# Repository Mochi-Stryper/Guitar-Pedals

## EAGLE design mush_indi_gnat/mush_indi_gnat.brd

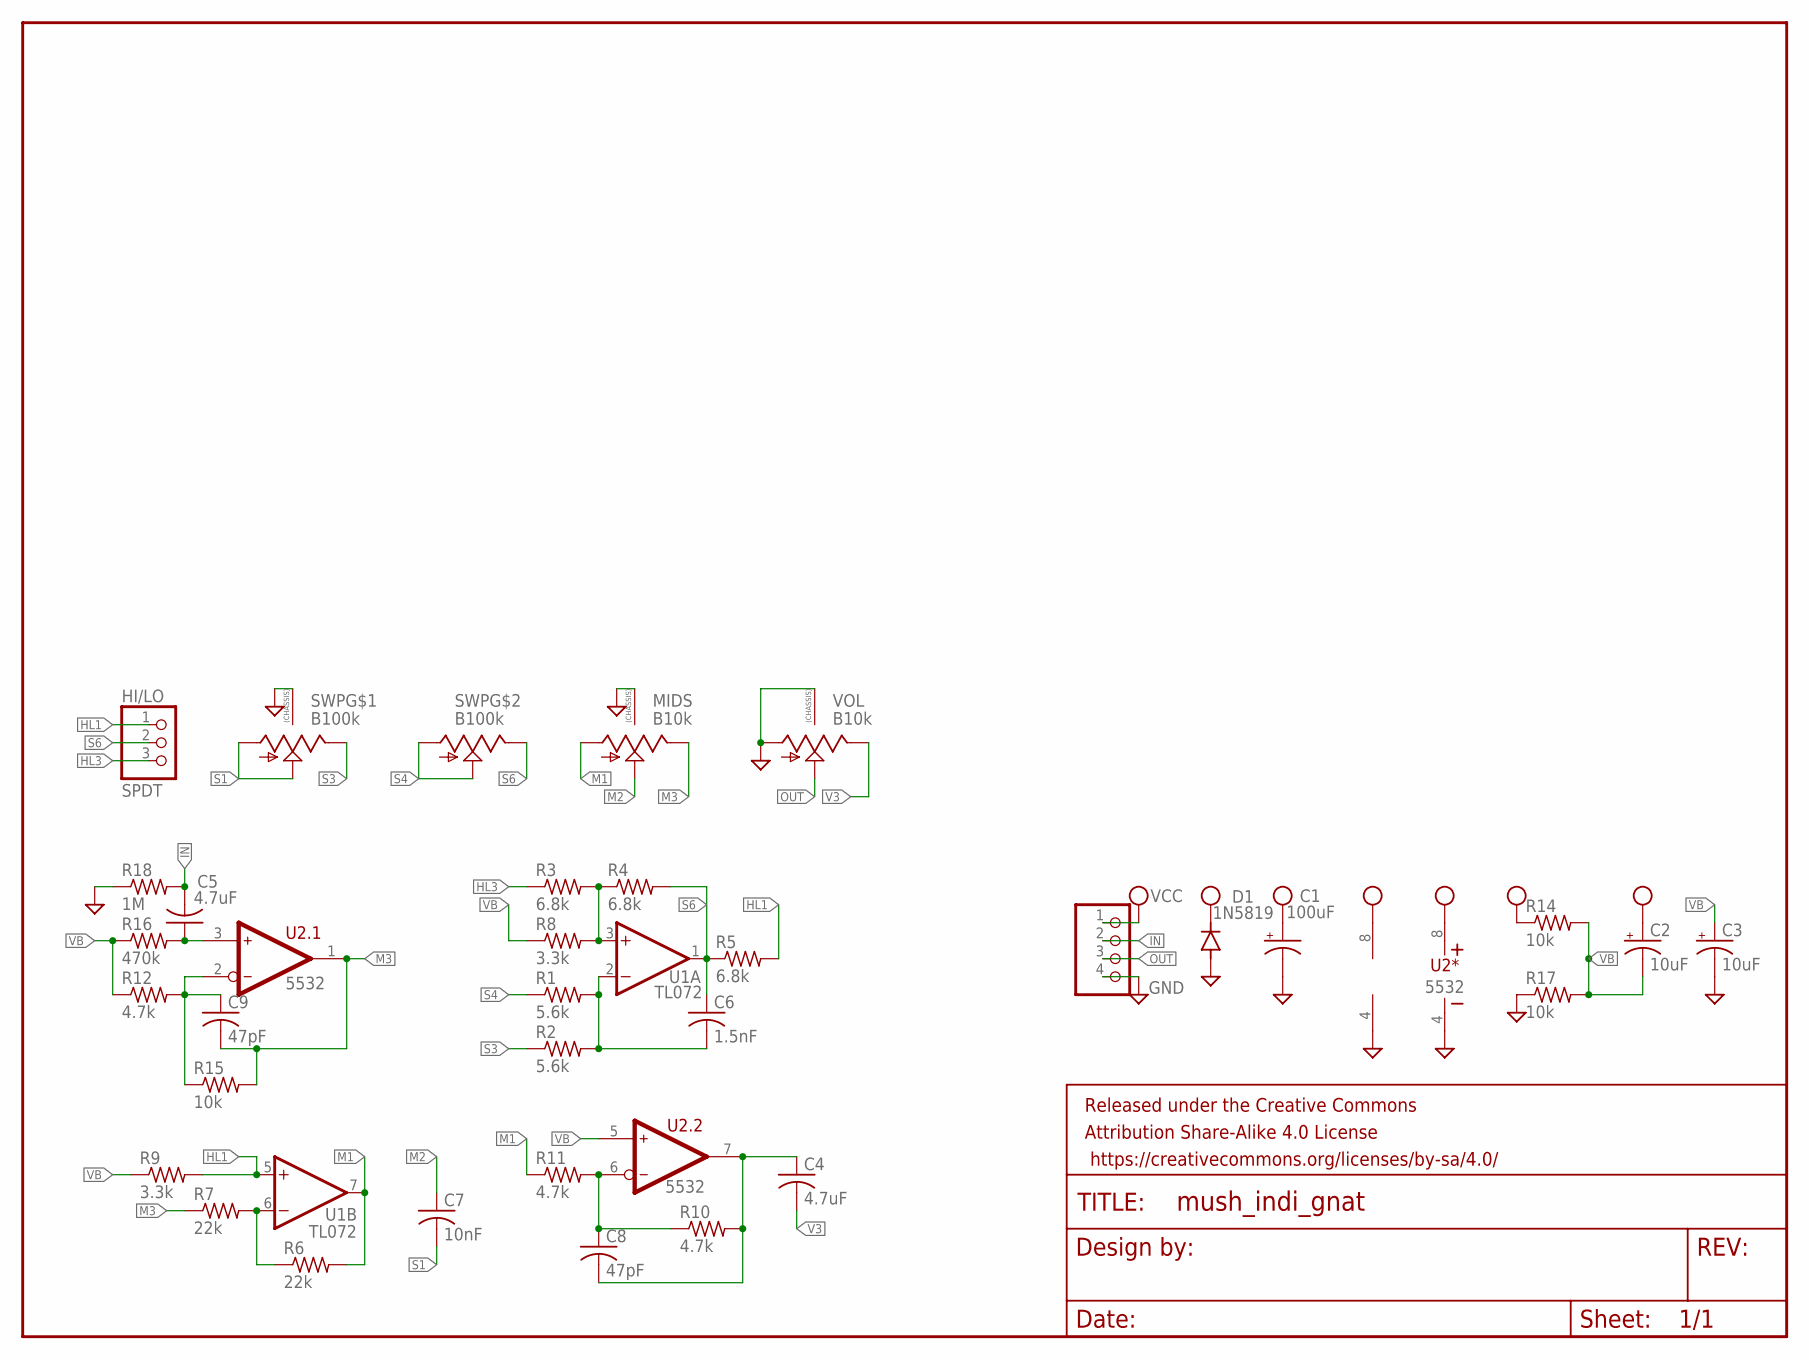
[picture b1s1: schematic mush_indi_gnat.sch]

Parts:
C1: 100uF; PAN_B_SMD+THRU
C2, C3: 10uF; CAPMP3216X180N
C4, C5: 4.7uF; C0805
C6: 1.5nF; C0603
C7: 10nF; C0603
C8, C9: 47pF; C0603
D1: 1N5819; SOD123
FRAME1: FRAME-LETTERNO_PACKAGE; DUMMY
HI/LO: SPDT; 1X03
JP1: PINHD-1X4; 1X04
MIDS: B10k; 9MM_SNAP-IN_POT
R1, R2: 5.6k; R0603
R3, R4, R5: 6.8k; R0603
R6, R7: 22k; R0603
R8, R9: 3.3k; R0603
R10, R11, R12: 4.7k; R0603
R14, R15, R17: 10k; R0603
R16: 470k; R0603
R18: 1M; R0603
SWP: B100k; DUAL_9MM_SNAP-IN_POT
U1: TL072; TSSOP-8
U2: 5532; SO-8
VOL: B10k; 9MM_SNAP-IN_POT

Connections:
GND: C1.-, C1.-- (-), C3.2 (-), D1.A, JP1.4, MIDS.CHASSIS1, MIDS.CHASSIS2, R17.1, R18.1, SWP.CHASSIS1, SWP.CHASSIS2, U1.4 (V-), U2.4 (V-), VOL.1 (A), VOL.CHASSIS1, VOL.CHASSIS2
HL1: HI/LO.1, R5.2, R9.2, U1.5 (+IN)
HL3: HI/LO.3, R3.1
IN: C5.2, JP1.2, R18.2
M1: MIDS.1 (A), R6.2, R11.1, U1.7 (OUT)
M2: C7.1, MIDS.2 (S)
M3: C9.2, MIDS.3 (E), R7.1, R15.2, U2.1 (OUT)
unnamed: C5.1, R16.2, U2.3 (IN+)
unnamed: C9.1, R12.2, R15.1, U2.2 (IN-)
unnamed: R6.1, R7.2, U1.6 (-IN)
unnamed: R3.2, R4.1, R8.2, U1.3 (+IN)
unnamed: C6.2, R1.2, R2.2, U1.2 (-IN)
unnamed: C8.1, R10.1, R11.2, U2.6 (IN-)
unnamed: C4.1, C8.2, R10.2, U2.7 (OUT)
OUT: JP1.3, VOL.2 (S)
S1: C7.2, SWP.1 (A), SWP.2 (S)
S3: R2.1, SWP.3 (E)
S4: R1.1, SWP.1B (A), SWP.2B (S)
S6: C6.1, HI/LO.2, R4.2, R5.1, SWP.3B (E), U1.1 (OUT)
V3: C4.2, VOL.3 (E)
VB: C2.2 (-), C3.1 (+), R8.1, R9.1, R12.1, R14.2, R16.1, R17.2, U2.5 (IN+)
VCC: C1.+, C1.++ (+), C2.1 (+), D1.C, JP1.1, R14.1, U1.8 (V+), U2.8 (V+)

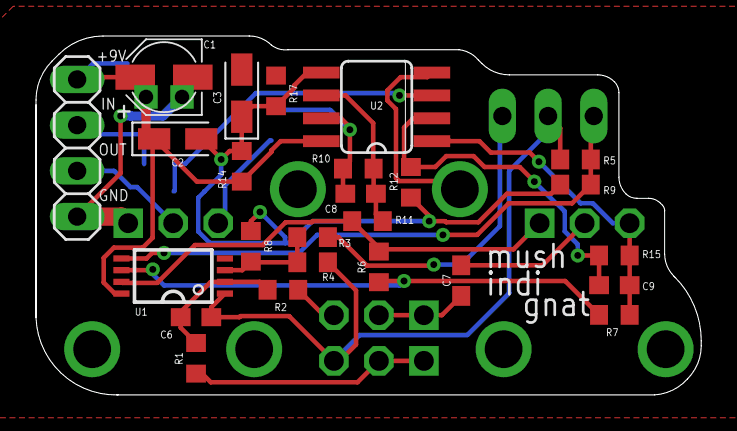
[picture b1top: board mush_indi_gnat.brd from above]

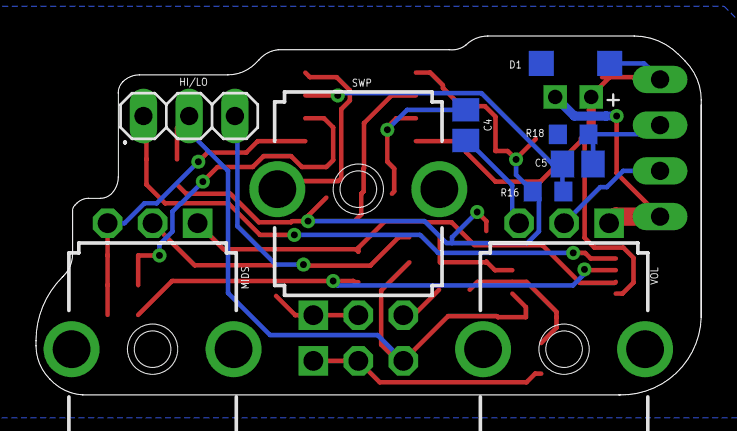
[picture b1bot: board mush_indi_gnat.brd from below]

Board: 2 copper layers, 37.0 x 19.9 mm, 35 parts (9 on the bottom side), 22 nets.

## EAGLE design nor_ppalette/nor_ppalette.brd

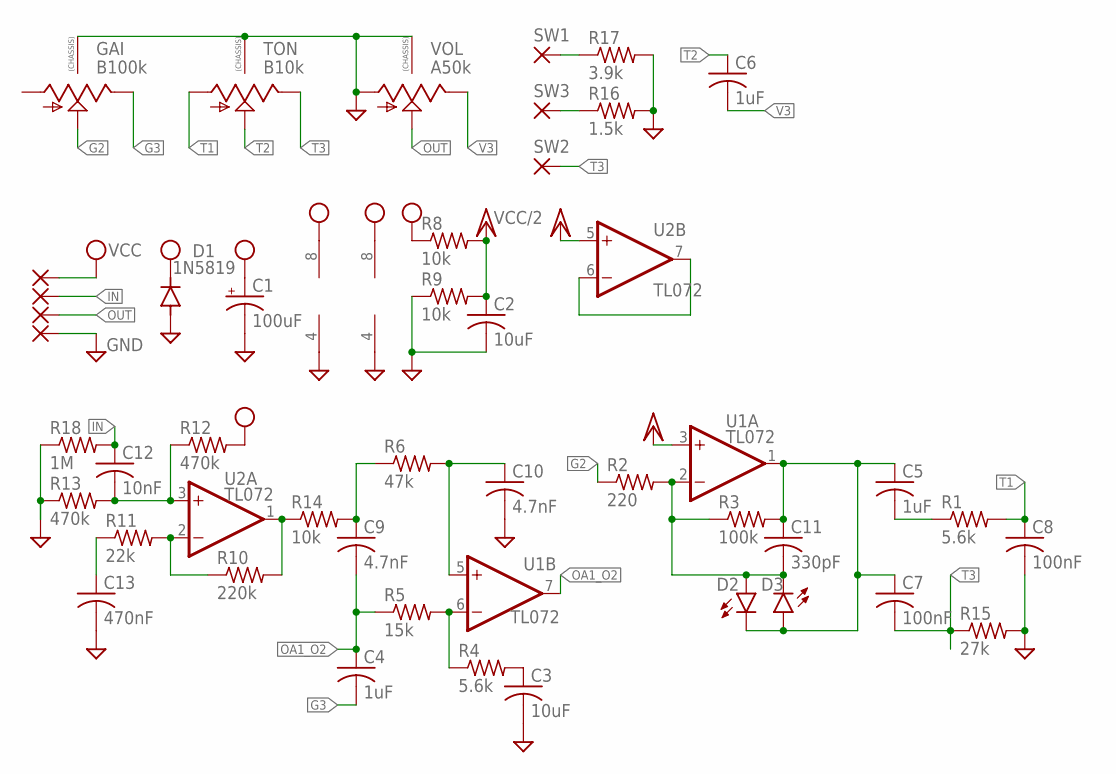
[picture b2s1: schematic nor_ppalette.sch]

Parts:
C1: 100uF; CPOL-RADIAL-2.5MM-6.5MM
C2, C3: 10uF; C1206
C4, C5, C6: 1uF; C0805
C7, C8: 100nF; C0603
C9, C10: 4.7nF; C0603
C11: 330pF; C0603
C12: 10nF; C0603
C13: 470nF; C0603
D1: 1N5819; SOD123
D2, D3: LED0603; LED-0603
GAI: B100k; 9MM_SNAP-IN_POT
PAD1, PAD2, PAD3, PAD4: 1,6/0,8
R1, R4: 5.6k; R0603
R2: 220; R0603
R3: 100k; R0603
R5: 15k; R0603
R6: 47k; R0603
R8, R9, R14: 10k; R0603
R10: 220k; R0603
R11: 22k; R0603
R12, R13: 470k; R0603
R15: 27k; R0603
R16: 1.5k; R0603
R17: 3.9k; R0603
R18: 1M; R0603
SW1, SW2, SW3: 1,6/0,8
TON: B10k; 9MM_SNAP-IN_POT
U1, U2: TL072; TSSOP-8
VOL: A50k; 9MM_SNAP-IN_POT

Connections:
G2: GAI.2 (S), R2.1
G3: C4.2, GAI.3 (E)
GND: C1.2 (-), C2.2, C3.2, C8.2, C10.2, C13.2, D1.A, GAI.CHASSIS1, GAI.CHASSIS2, PAD4.1, R9.1, R13.1, R15.2, R16.2, R17.2, R18.1, TON.CHASSIS1, TON.CHASSIS2, U1.4 (V-), U2.4 (V-), VOL.1 (A), VOL.CHASSIS1, VOL.CHASSIS2
IN: C12.1, PAD2.1, R18.2
unnamed: R10.1, R11.2, U2.2 (-IN)
unnamed: U2.6 (-IN), U2.7 (OUT)
unnamed: C12.2, R12.1, R13.2, U2.3 (+IN)
unnamed: R10.2, R14.1, U2.1 (OUT)
unnamed: C13.1, R11.1
unnamed: C9.1, R6.1, R14.2
unnamed: C10.1, R6.2, U1.5 (+IN)
unnamed: R4.1, R5.2, U1.6 (-IN)
unnamed: C3.1, R4.2
unnamed: C5.1, C7.1, C11.1, D2.C, D3.A, R3.2, U1.1 (OUT)
unnamed: C11.2, D2.A, D3.C, R2.2, R3.1, U1.2 (-IN)
unnamed: C5.2, R1.1
unnamed: R17.1, SW1.1
unnamed: R16.1, SW3.1
OA1_O2: C4.1, C9.2, R5.1, U1.7 (OUT)
OUT: PAD3.1, VOL.2 (S)
T1: C8.1, R1.2, TON.1 (A)
T2: C6.1, TON.2 (S)
T3: C7.2, R15.1, SW2.1, TON.3 (E)
V3: C6.2, VOL.3 (E)
VCC: C1.1 (+), D1.C, PAD1.1, R8.1, R12.2, U1.8 (V+), U2.8 (V+)
VCC/2: C2.1, R8.2, R9.2, U1.3 (+IN), U2.5 (+IN)

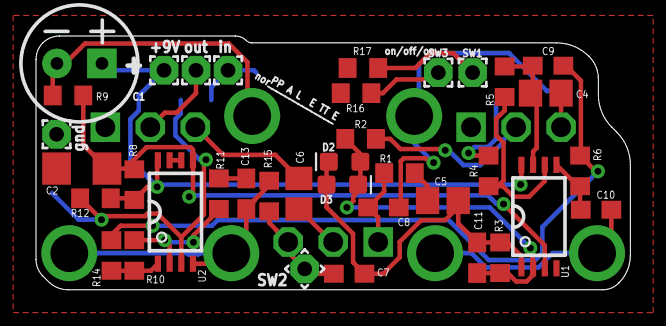
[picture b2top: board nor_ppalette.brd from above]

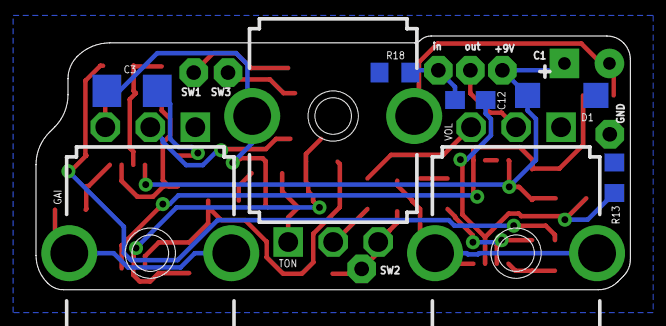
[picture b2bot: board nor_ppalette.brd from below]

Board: 2 copper layers, 33.0 x 14.1 mm, 45 parts (8 on the bottom side), 26 nets.

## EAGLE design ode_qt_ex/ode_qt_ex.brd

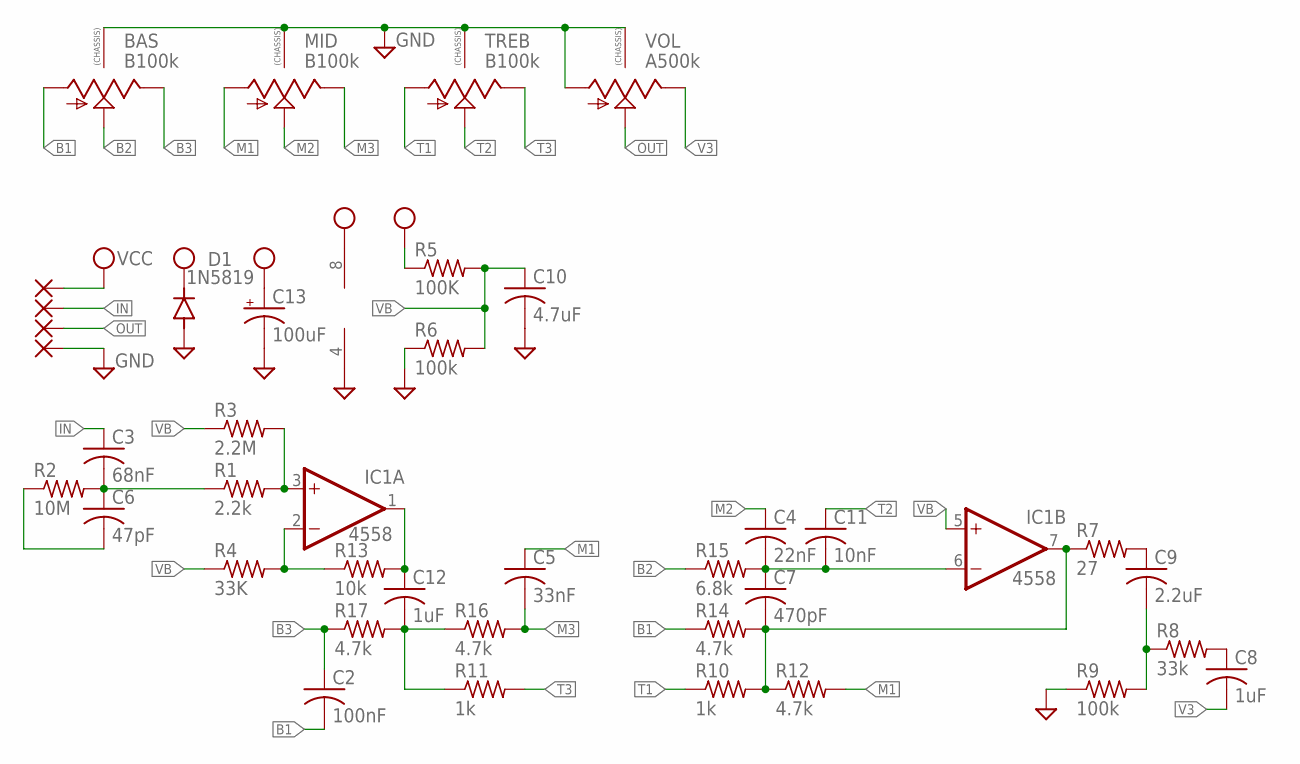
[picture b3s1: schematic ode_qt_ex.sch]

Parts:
BAS: B100k; 9MM_SNAP-IN_POT
C2: 100nF; C0603
C3: 68nF; C0603
C4: 22nF; C0603
C5: 33nF; C0603
C6: 47pF; C0603
C7: 470pF; C0603
C8, C12: 1uF; C0603
C9: 2.2uF; C0805
C10: 4.7uF; C0805
C11: 10nF; C0603
C13: 100uF; CPOL-RADIAL-2.5MM-6.5MM
D1: 1N5819; SOD123
IC1: 4558; SO08
MID: B100k; 9MM_SNAP-IN_POT
PAD1, PAD2, PAD3, PAD4: 1,6/0,8
R1: 2.2k; R0603
R2: 10M; R0603
R3: 2.2M; R0603
R4: 33K; R0603
R5: 100K; R0603
R6, R9: 100k; R0603
R7: 27; R0603
R8: 33k; R0603
R10, R11: 1k; R0603
R12, R14, R16, R17: 4.7k; R0603
R13: 10k; R0603
R15: 6.8k; R0603
TREB: B100k; 9MM_SNAP-IN_POT
VOL: A500k; 9MM_SNAP-IN_POT

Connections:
B1: BAS.1 (A), C2.2, R14.1
B2: BAS.2 (S), R15.1
B3: BAS.3 (E), C2.1, R17.1
GND: BAS.CHASSIS1, BAS.CHASSIS2, C10.2, C13.2 (-), D1.A, IC1.4 (V-), MID.CHASSIS1, MID.CHASSIS2, PAD4.1, R6.1, R9.1, TREB.CHASSIS1, TREB.CHASSIS2, VOL.1 (A), VOL.CHASSIS1, VOL.CHASSIS2
IN: C3.1, PAD2.1
M1: C5.1, MID.1 (A), R12.2
M2: C4.1, MID.2 (S)
M3: C5.2, MID.3 (E), R16.2
unnamed: C3.2, C6.1, R1.1, R2.2
unnamed: C6.2, R2.1
unnamed: IC1.3 (+IN), R1.2, R3.2
unnamed: C12.1, IC1.1 (OUT), R13.2
unnamed: IC1.2 (-IN), R4.2, R13.1
unnamed: C12.2, R11.1, R16.1, R17.2
unnamed: C4.2, C7.1, C11.2, IC1.6 (-IN), R15.2
unnamed: C7.2, IC1.7 (OUT), R7.1, R10.2, R12.1, R14.2
unnamed: C9.1, R7.2
unnamed: C9.2, R8.1, R9.2
unnamed: C8.1, R8.2
OUT: PAD3.1, VOL.2 (S)
T1: R10.1, TREB.1 (A)
T2: C11.1, TREB.2 (S)
T3: R11.2, TREB.3 (E)
V3: C8.2, VOL.3 (E)
VB: C10.1, IC1.5 (+IN), R3.1, R4.1, R5.2, R6.2
VCC: C13.1 (+), D1.C, IC1.8 (V+), PAD1.1, R5.1

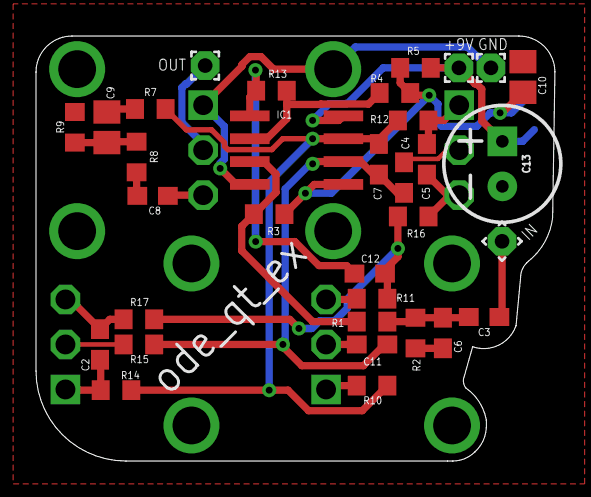
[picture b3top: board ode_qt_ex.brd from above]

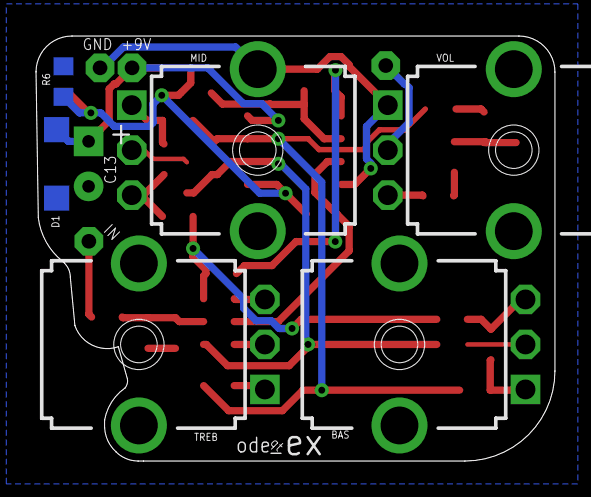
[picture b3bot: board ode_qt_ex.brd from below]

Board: 2 copper layers, 28.8 x 23.6 mm, 39 parts (6 on the bottom side), 26 nets.

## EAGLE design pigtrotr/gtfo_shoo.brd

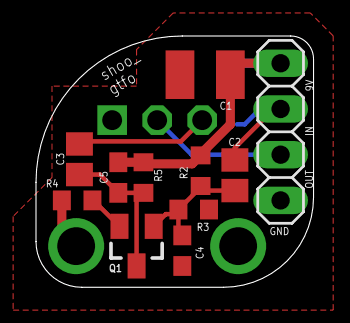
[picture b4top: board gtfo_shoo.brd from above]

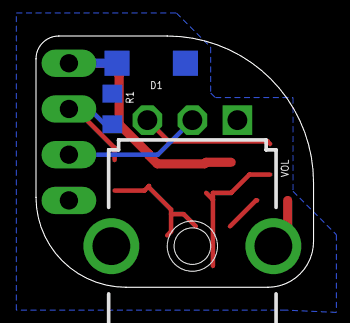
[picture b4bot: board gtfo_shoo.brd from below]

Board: 2 copper layers, 15.4 x 14.0 mm, 14 parts (3 on the bottom side), 8 nets.

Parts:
C1: 47uF; C1210
C2, C3: 3.3uF; C0805
C4, C5: 100nF; C0603
D1: 1N5819; SOD123
JP1: 1X04
Q1: MMBT5088; SOT23-BEC
R1: 1.5M; R0603
R2: 430k; R0603
R3: 43k; R0603
R4: 390; R0603
R5: 10k; R0603
VOL: A100k; 9MM_SNAP-IN_POT

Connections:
GND: C1.2, C4.2, D1.A, JP1.4, R1.1, R3.1, R4.2, VOL.1, VOL.CHASSIS1, VOL.CHASSIS2
IN: C2.1, JP1.2, R1.2
unnamed: C2.2, C4.1, Q1.B, R2.2, R3.2
unnamed: C3.2, C5.2, Q1.C, R5.1
unnamed: Q1.E, R4.1
OUT: JP1.3, VOL.2
V3: C3.1, VOL.3
VCC: C1.1, C5.1, D1.C, JP1.1, R2.1, R5.2

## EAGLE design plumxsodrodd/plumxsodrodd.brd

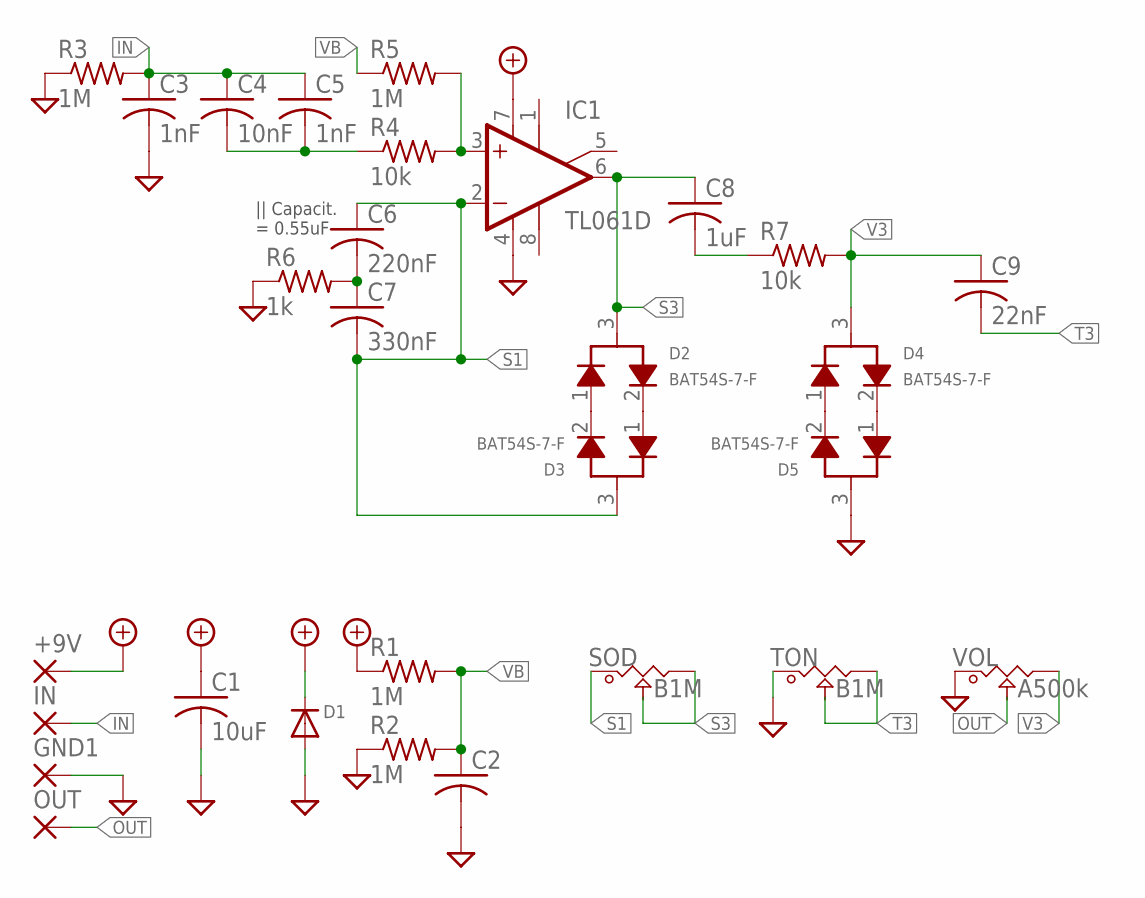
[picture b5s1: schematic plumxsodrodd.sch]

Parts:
+9V: SMD2; SMD1,27-2,54
C1: 10uF; C1206
C2: C-USC0603; C0603
C3, C5: 1nF; C0603
C4: 10nF; C0603
C6: 220nF; C0603
C7: 330nF; C0603
C8: 1uF; C0603
C9: 22nF; C0603
D1: DIODESOD-123; SOD-123
D2, D3, D4, D5: BAT54S-7-F; SOT23-3
GND1: SMD2; SMD1,27-2,54
IC1: TL061D; SO08
IN: SMD2; SMD1,27-2,54
OUT: SMD2; SMD1,27-2,54
R1, R2, R3, R5: 1M; R0603
R4, R7: 10k; R0603
R6: 1k; R0603
SOD: B1M; POT_9MM_SMD
TON: B1M; POT_9MM_SMD
VOL: A500k; POT_9MM_SMD

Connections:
+9V: +9V.1, C1.1, D1.C, IC1.7 (V+), R1.1
GND: C1.2, C2.2, C3.2, D1.A, D5.3, GND1.1, IC1.4 (V-), R2.1, R3.1, R6.1, TON.1, VOL.1
IN: C3.1, C4.1, C5.1, IN.1, R3.2
unnamed: C4.2, C5.2, R4.1
unnamed: IC1.3 (+IN), R4.2, R5.2
unnamed: D2.2, D3.1
unnamed: C6.2, C7.1, R6.2
unnamed: D2.1, D3.2
unnamed: C8.2, R7.1
unnamed: D4.2, D5.1
unnamed: D4.1, D5.2
OUT: OUT.1, VOL.2
S1: C6.1, C7.2, D3.3, IC1.2 (-IN), SOD.1
S3: C8.1, D2.3, IC1.6 (OUT), SOD.2, SOD.3
T3: C9.2, TON.2, TON.3
V3: C9.1, D4.3, R7.2, VOL.3
VB: C2.1, R1.2, R2.2, R5.1

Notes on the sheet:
|| Capacit. = 0.55uF

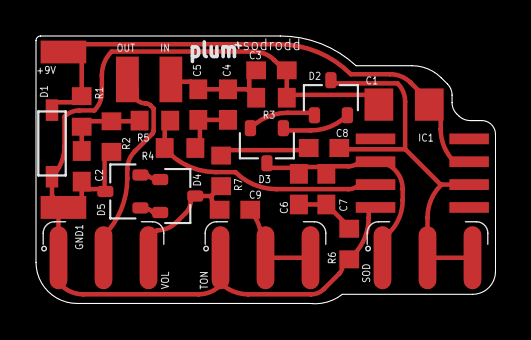
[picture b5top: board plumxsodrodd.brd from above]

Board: 2 copper layers, 25.5 x 14.9 mm, 29 parts (0 on the bottom side), 17 nets.

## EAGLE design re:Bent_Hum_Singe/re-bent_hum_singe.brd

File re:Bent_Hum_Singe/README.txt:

Valvewizard
Engineer's Thumb Compressor

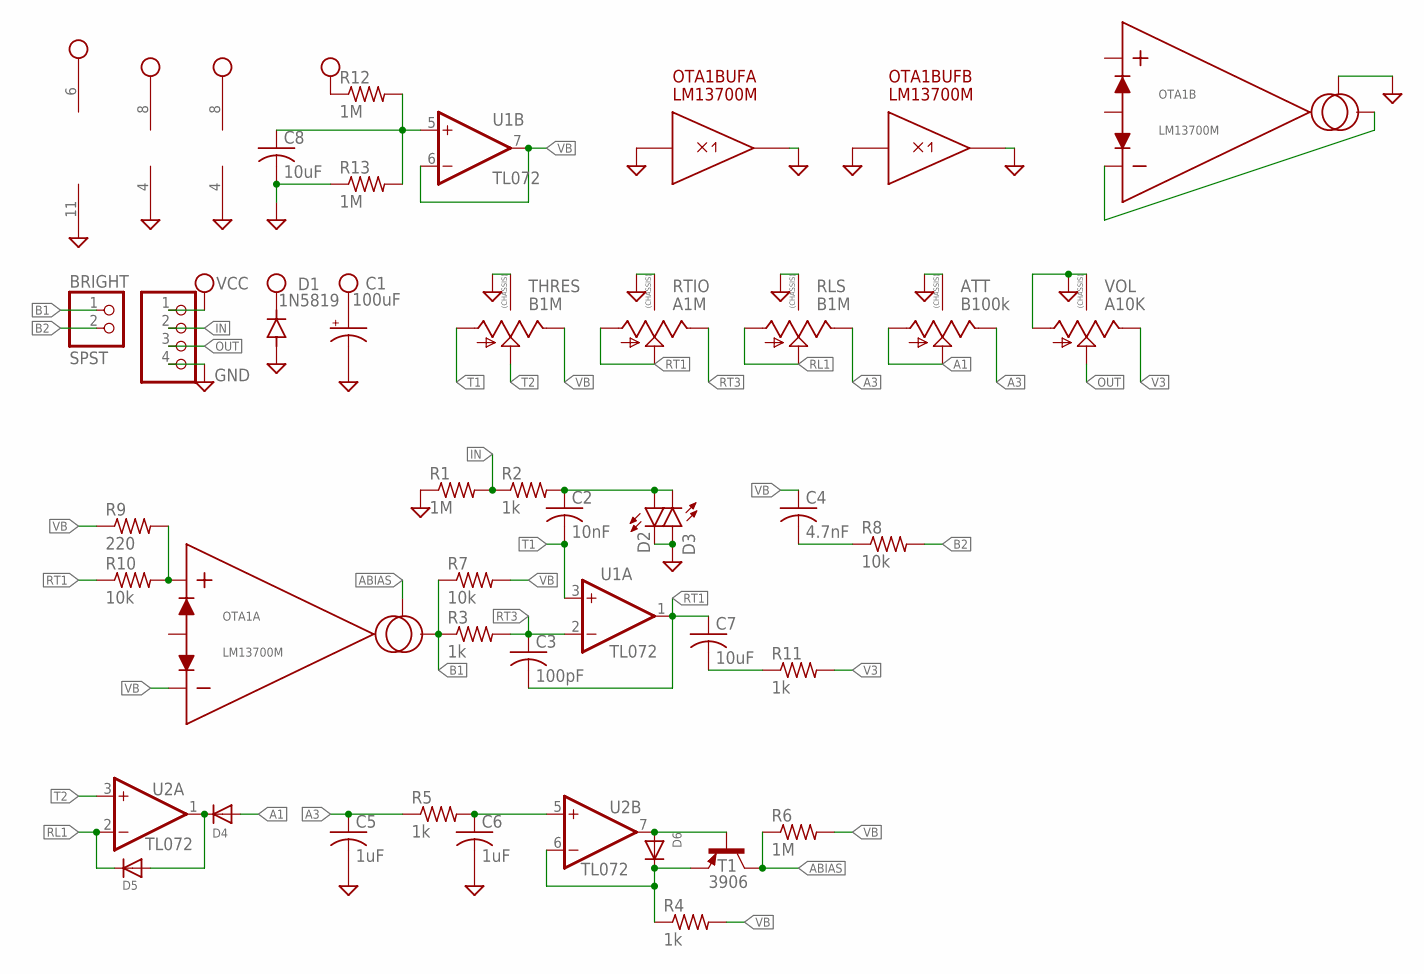
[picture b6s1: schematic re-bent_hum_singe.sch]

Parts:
ATT: B100k; 9MM_SNAP-IN_POT
BRIGHT: SPST; 1X02
C1: 100uF; PAN_B_SMD+THRU
C2: 10nF; C0603
C3: 100pF; C0603
C4: 4.7nF; C0603
C5, C6: 1uF; C0805
C7, C8: 10uF; C1206
D1: 1N5819; SOD123
D2, D3: LED0603; LED-0603
D4, D5, D6: DIODESOD-123; SOD-123
JP1: PINHD-1X4; 1X04
OTA1: LM13700M; SO16
R1, R6, R12, R13: 1M; R0603
R2, R3, R4, R5, R11: 1k; R0603
R7, R8, R10: 10k; R0603
R9: 220; R0603
RLS: B1M; 9MM_SNAP-IN_POT
RTIO: A1M; 9MM_SNAP-IN_POT
T1: 3906; SOT23-BEC
THRES: B1M; 9MM_SNAP-IN_POT
U1, U2: TL072; TSSOP-8
VOL: A10K; 9MM_SNAP-IN_POT

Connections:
A1: ATT.1 (A), ATT.2 (S), D4.A
A3: ATT.3 (E), C5.1, R5.1, RLS.3 (E)
ABIAS: OTA1.1 (IABC), R6.1, T1.C
B1: BRIGHT.1, OTA1.5 (IOUT), R3.1, R7.1
B2: BRIGHT.2, R8.2
GND: ATT.CHASSIS1, ATT.CHASSIS2, C1.-, C1.-- (-), C5.2, C6.2, C8.2, D1.A, D2.C, D3.A, JP1.4, OTA1.8 (OUT), OTA1.9 (OUT), OTA1.11 (VEE), OTA1.16 (IABC), R1.1, R13.1, RLS.CHASSIS1, RLS.CHASSIS2, RTIO.CHASSIS1, RTIO.CHASSIS2, THRES.CHASSIS1, THRES.CHASSIS2, U1.4 (V-), U2.4 (V-), VOL.1 (A), VOL.CHASSIS1, VOL.CHASSIS2
IN: JP1.2, R1.2, R2.1
unnamed: C8.1, R12.2, R13.2, U1.5 (+IN)
unnamed: C2.1, D2.A, D3.C, R2.2
unnamed: OTA1.3 (IN+), R9.2, R10.2
unnamed: C7.2, R11.1
unnamed: D4.C, D5.A, U2.1 (OUT)
unnamed: OTA1.12 (IOUT), OTA1.13 (IN-)
unnamed: C6.1, R5.2, U2.5 (+IN)
unnamed: D6.C, R4.1, T1.E, U2.6 (-IN)
unnamed: D6.A, T1.B, U2.7 (OUT)
unnamed: C4.2, R8.1
OUT: JP1.3, VOL.2 (S)
RL1: D5.C, RLS.1 (A), RLS.2 (S), U2.2 (-IN)
RT1: C3.2, C7.1, R10.1, RTIO.1 (A), RTIO.2 (S), U1.1 (OUT)
RT3: C3.1, R3.2, RTIO.3 (E), U1.2 (-IN)
T1: C2.2, THRES.1 (A), U1.3 (+IN)
T2: THRES.2 (S), U2.3 (+IN)
V3: R11.2, VOL.3 (E)
VB: C4.1, OTA1.4 (IN-), R4.2, R6.2, R7.2, R9.1, THRES.3 (E), U1.6 (-IN), U1.7 (OUT)
VCC: C1.+, C1.++ (+), D1.C, JP1.1, OTA1.6 (VCC), R12.1, U1.8 (V+), U2.8 (V+)

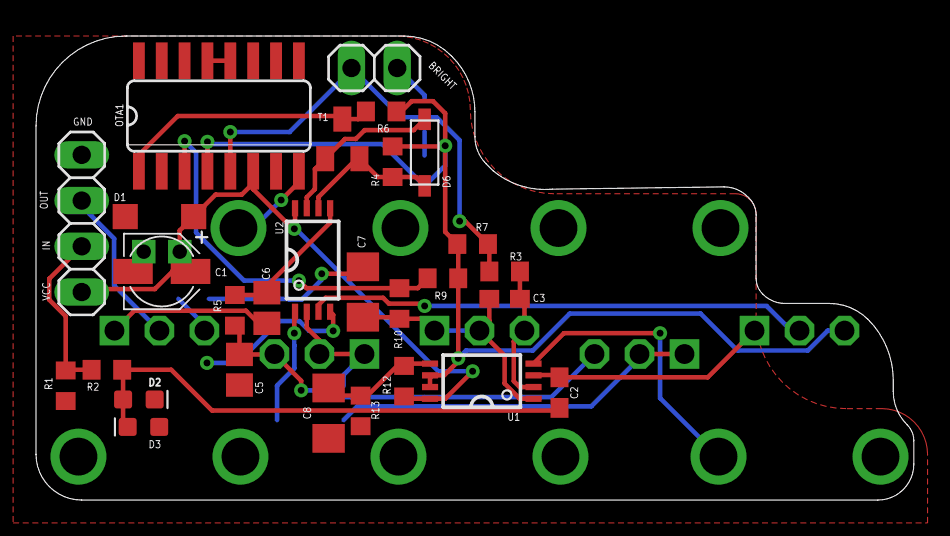
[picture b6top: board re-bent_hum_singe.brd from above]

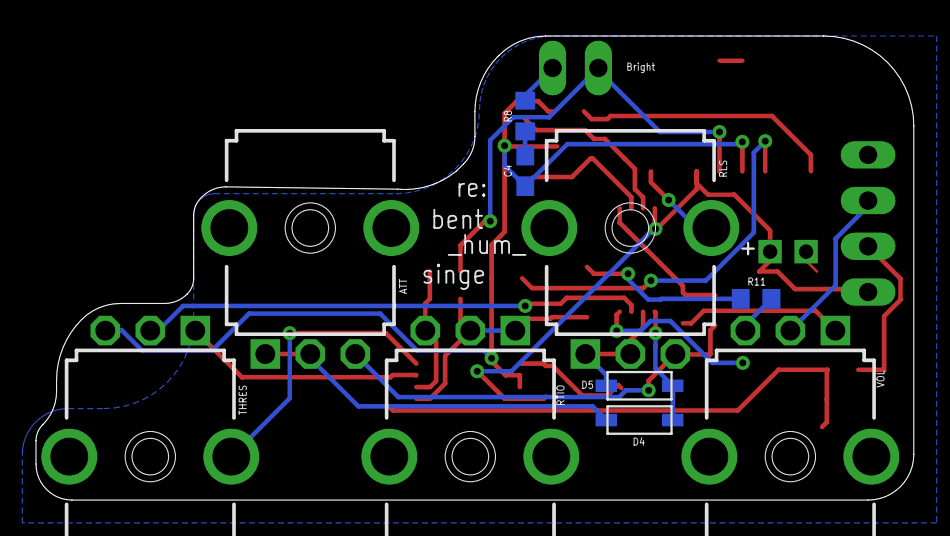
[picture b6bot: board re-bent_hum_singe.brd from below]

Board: 2 copper layers, 48.8 x 25.8 mm, 38 parts (10 on the bottom side), 26 nets.

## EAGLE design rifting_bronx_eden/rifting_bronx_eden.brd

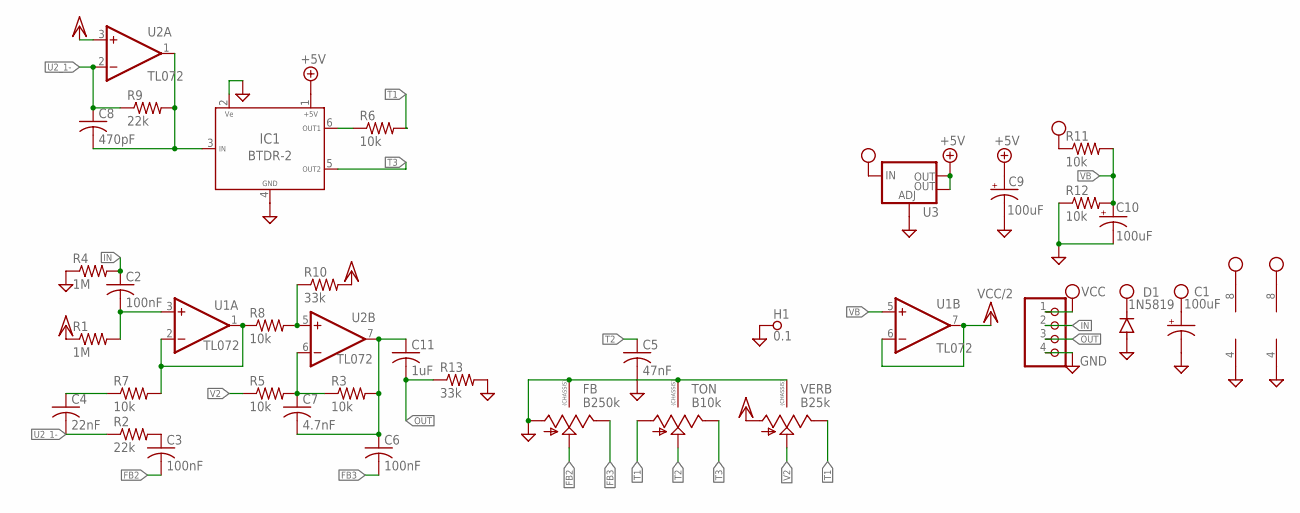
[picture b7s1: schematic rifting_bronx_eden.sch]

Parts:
C1, C9, C10: 100uF; PAN_B_SMD+THRU
C2, C3, C6: 100nF; C0603
C4: 22nF; C0603
C5: 47nF; C0603
C7: 4.7nF; C0603
C8: 470pF; C0603
C11: 1uF; C0603
D1: 1N5819; SOD123
FB: B250k; 9MM_SNAP-IN_POT
H1: 0.1; PAD_0.1000
IC1: BTDR-2
JP1: PINHD-1X4; 1X04
R1, R4: 1M; R0603
R2, R9: 22k; R0603
R3, R5, R6, R7, R8, R11, R12: 10k; R0603
R10, R13: 33k; R0603
TON: B10k; 9MM_SNAP-IN_POT
U1, U2: TL072; TSSOP-8
U3: V_REG_LM1117SOT223; SOT223
VERB: B25k; 9MM_SNAP-IN_POT

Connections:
+5V: C9.+, C9.++ (+), IC1.1, U3.2 (OUT), U3.4 (OUT)
FB2: C3.2, FB.2 (S)
FB3: C6.2, FB.3 (E)
GND: C1.-, C1.-- (-), C5.2, C9.-, C9.-- (-), C10.-, C10.-- (-), D1.A, FB.1 (A), FB.CHASSIS1, FB.CHASSIS2, H1.1, IC1.2, IC1.4, JP1.4, R4.1, R12.1, R13.2, TON.CHASSIS1, TON.CHASSIS2, U1.4 (V-), U2.4 (V-), U3.1 (ADJ), VERB.CHASSIS1, VERB.CHASSIS2
IN: C2.1, JP1.2, R4.2
unnamed: C4.1, R7.1
unnamed: C2.2, R1.2, U1.3 (+IN)
unnamed: R7.2, R8.1, U1.1 (OUT), U1.2 (-IN)
unnamed: C3.1, R2.2
unnamed: R8.2, R10.1, U2.5 (+IN)
unnamed: C7.1, R3.1, R5.2, U2.6 (-IN)
unnamed: C6.1, C7.2, C11.1, R3.2, U2.7 (OUT)
unnamed: IC1.6, R6.1
unnamed: C8.2, IC1.3, R9.2, U2.1 (OUT)
OUT: C11.2, JP1.3, R13.1
T1: R6.2, TON.1 (A), VERB.3 (E)
T2: C5.1, TON.2 (S)
T3: IC1.5, TON.3 (E)
U2_1-: C4.2, C8.1, R2.1, R9.1, U2.2 (-IN)
V2: R5.1, VERB.2 (S)
VB: C10.+, C10.++ (+), R11.2, R12.2, U1.5 (+IN)
VCC: C1.+, C1.++ (+), D1.C, JP1.1, R11.1, U1.8 (V+), U2.8 (V+), U3.3 (IN)
VCC/2: R1.1, R10.2, U1.6 (-IN), U1.7 (OUT), U2.3 (+IN), VERB.1 (A)

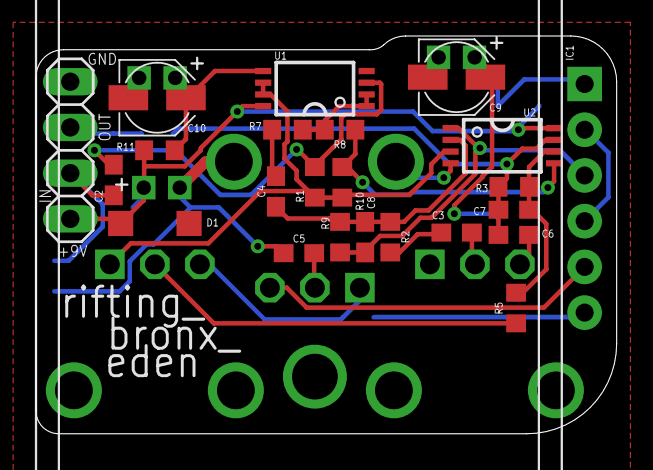
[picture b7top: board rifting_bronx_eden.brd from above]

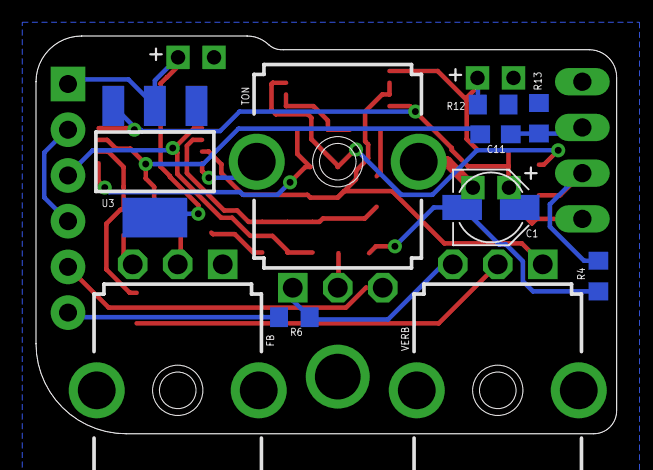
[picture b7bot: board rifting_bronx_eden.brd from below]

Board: 2 copper layers, 32.3 x 22.1 mm, 34 parts (10 on the bottom side), 23 nets.

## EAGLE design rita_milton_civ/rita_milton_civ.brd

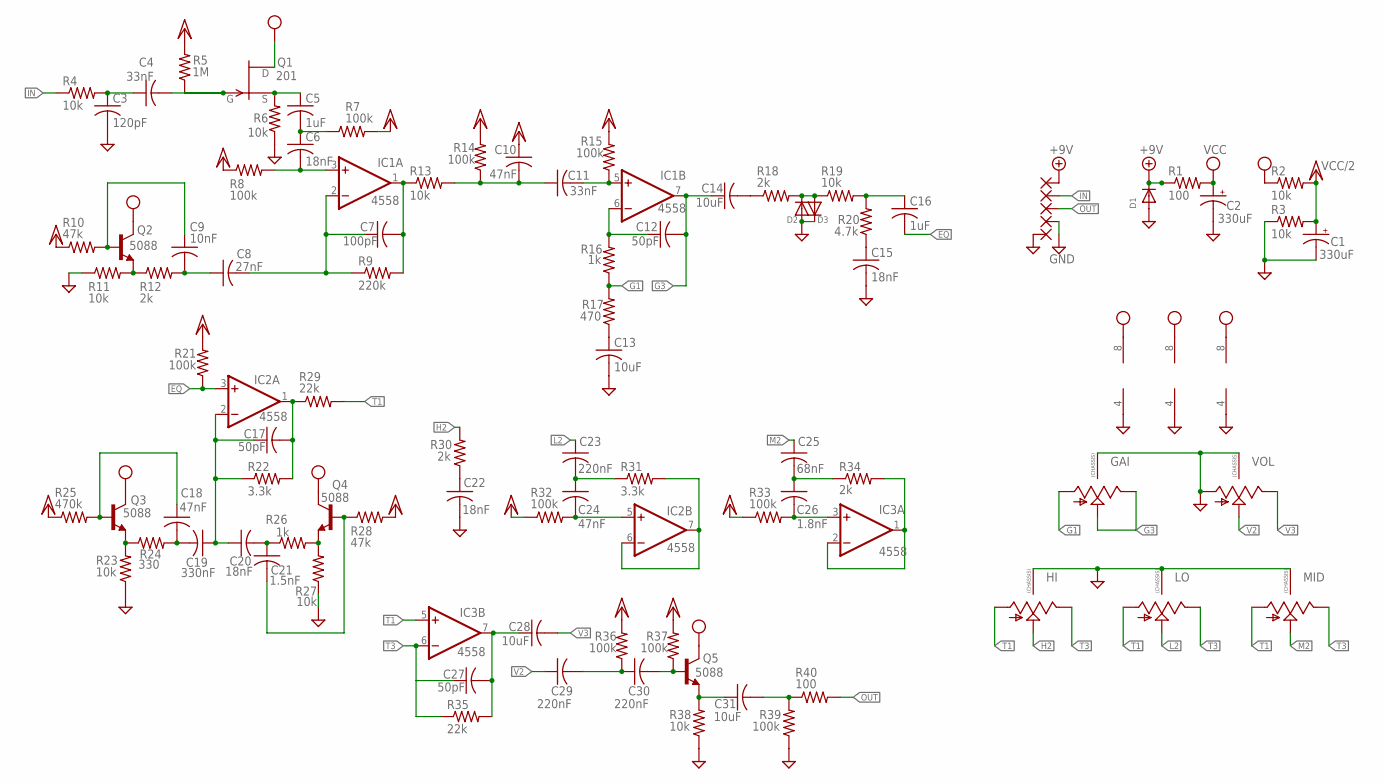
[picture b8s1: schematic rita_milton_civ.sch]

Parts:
C1, C2: 330uF; 080_035
C3: 120pF; C0603
C4, C11: 33nF; C0603
C5, C16: 1uF; C0805
C6, C15, C20, C22: 18nF; C0603
C7: 100pF; C0603
C8: 27nF; C0603
C9: 10nF; C0603
C10, C18, C24: 47nF; C0603
C12, C17, C27: 50pF; C0603
C13, C14, C28, C31: 10uF; C1206
C19: 330nF; C0603
C21: 1.5nF; C0603
C23, C29, C30: 220nF; C0603
C25: 68nF; C0603
C26: 1.8nF; C0603
D1, D2, D3: DIODESOD-123; SOD-123
GAI: 9MM_SNAP-IN_POT_CHASSIS; 9MM_SNAP-IN_POT
HI: 9MM_SNAP-IN_POT_CHASSIS; 9MM_SNAP-IN_POT
IC1, IC2, IC3: 4558; SO08
LO: 9MM_SNAP-IN_POT_CHASSIS; 9MM_SNAP-IN_POT
MID: 9MM_SNAP-IN_POT_CHASSIS; 9MM_SNAP-IN_POT
PAD1, PAD2, PAD3, PAD4, PAD5: 1,6/0,8
Q1: 201; SOT23
Q2, Q3, Q4, Q5: 5088; SOT23
R1: 100; R0805
R2, R3, R4, R6, R11, R13, R19, R23, R27, R38: 10k; R0603
R5: 1M; R0603
R7, R8, R14, R15, R21, R32, R33, R36, R37, R39: 100k; R0603
R9: 220k; R0603
R10, R28: 47k; R0603
R12, R18, R30, R34: 2k; R0603
R16, R26: 1k; R0603
R17: 470; R0603
R20: 4.7k; R0603
R22, R31: 3.3k; R0603
R24: 330; R0603
R25: 470k; R0603
R29, R35: 22k; R0603
R40: 100; R0603
VOL: 9MM_SNAP-IN_POT_CHASSIS; 9MM_SNAP-IN_POT

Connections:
+9V: D1.C, PAD1.1, R1.1
EQ: C16.2, IC2.3 (+IN), R21.1
G1: GAI.1 (A), R16.1, R17.2
G3: C12.2, C14.1, GAI.2 (S), GAI.3 (E), IC1.7 (OUT)
GND: C1.-, C2.-, C3.2, C13.2, C15.2, C22.2, D1.A, D2.A, D3.C, GAI.CHASSIS1, GAI.CHASSIS2, HI.CHASSIS1, HI.CHASSIS2, IC1.4 (V-), IC2.4 (V-), IC3.4 (V-), LO.CHASSIS1, LO.CHASSIS2, MID.CHASSIS1, MID.CHASSIS2, PAD4.1, PAD5.1, R3.1, R6.1, R11.1, R23.1, R27.1, R38.1, R39.1, VOL.1 (A), VOL.CHASSIS1, VOL.CHASSIS2
H2: HI.2 (S), R30.2
IN: PAD2.1, R4.1
L2: C23.1, LO.2 (S)
M2: C25.1, MID.2 (S)
unnamed: C3.1, C4.1, R4.2
unnamed: C4.2, Q1.3 (G), R5.1
unnamed: C5.1, Q1.2 (S), R6.2
unnamed: C5.2, C6.1, R7.1
unnamed: C6.2, IC1.3 (+IN), R8.2
unnamed: C9.1, Q2.1 (B), R10.2
unnamed: Q2.2 (E), R11.2, R12.1
unnamed: C8.1, C9.2, R12.2
unnamed: C7.1, C8.2, IC1.2 (-IN), R9.1
unnamed: C7.2, IC1.1 (OUT), R9.2, R13.1
unnamed: C10.2, C11.1, R13.2, R14.1
unnamed: C11.2, IC1.5 (+IN), R15.1
unnamed: C12.1, IC1.6 (-IN), R16.2
unnamed: C14.2, R18.1
unnamed: D2.C, D3.A, R18.2, R19.1
unnamed: C13.1, R17.1
unnamed: C17.1, C19.1, C20.1, IC2.2 (-IN), R22.1
unnamed: C16.1, R19.2, R20.2
unnamed: C15.1, R20.1
unnamed: C17.2, IC2.1 (OUT), R22.2, R29.1
unnamed: Q3.2 (E), R23.2, R24.1
unnamed: C18.2, C19.2, R24.2
unnamed: C18.1, Q3.1 (B), R25.2
unnamed: C20.2, C21.1, R26.1
unnamed: Q4.2 (E), R26.2, R27.2
unnamed: C21.2, Q4.1 (B), R28.1
unnamed: C22.1, R30.1
unnamed: C23.2, C24.1, R31.1
unnamed: C24.2, IC2.5 (+IN), R32.2
unnamed: IC2.6 (-IN), IC2.7 (OUT), R31.2
unnamed: C25.2, C26.1, R34.1
unnamed: C26.2, IC3.3 (+IN), R33.2
unnamed: IC3.1 (OUT), IC3.2 (-IN), R34.2
unnamed: C27.2, C28.1, IC3.7 (OUT), R35.2
unnamed: C29.2, C30.1, R36.1
unnamed: C30.2, Q5.1 (B), R37.1
unnamed: C31.1, Q5.2 (E), R38.2
unnamed: C31.2, R39.2, R40.1
OUT: PAD3.1, R40.2
T1: HI.1 (A), IC3.5 (+IN), LO.1 (A), MID.1 (A), R29.2
T3: C27.1, HI.3 (E), IC3.6 (-IN), LO.3 (E), MID.3 (E), R35.1
V2: C29.1, VOL.2 (S)
V3: C28.2, VOL.3 (E)
VCC: C2.+, IC1.8 (V+), IC2.8 (V+), IC3.8 (V+), Q1.1 (D), Q2.3 (C), Q3.3 (C), Q4.3 (C), Q5.3 (C), R1.2, R2.1
VCC/2: C1.+, C10.1, R2.2, R3.2, R5.2, R7.2, R8.1, R10.1, R14.2, R15.2, R21.2, R25.1, R28.2, R32.1, R33.1, R36.2, R37.2

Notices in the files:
parts and their libraries:
SparkFun-Aesthetics: Licensing: Creative Commons ShareAlike 4.0 International - https://creativecommons.org/licenses/by-sa/4.0
SparkFun-Aesthetics: Released under the Creative Commons Attribution Share-Alike 4.0 License
SparkFun-Aesthetics: https://creativecommons.org/licenses/by-sa/4.0
